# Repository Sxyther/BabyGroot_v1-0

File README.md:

# BabyGroot_v1-0
Babygroot project. Arduino based watering system for indoor plants

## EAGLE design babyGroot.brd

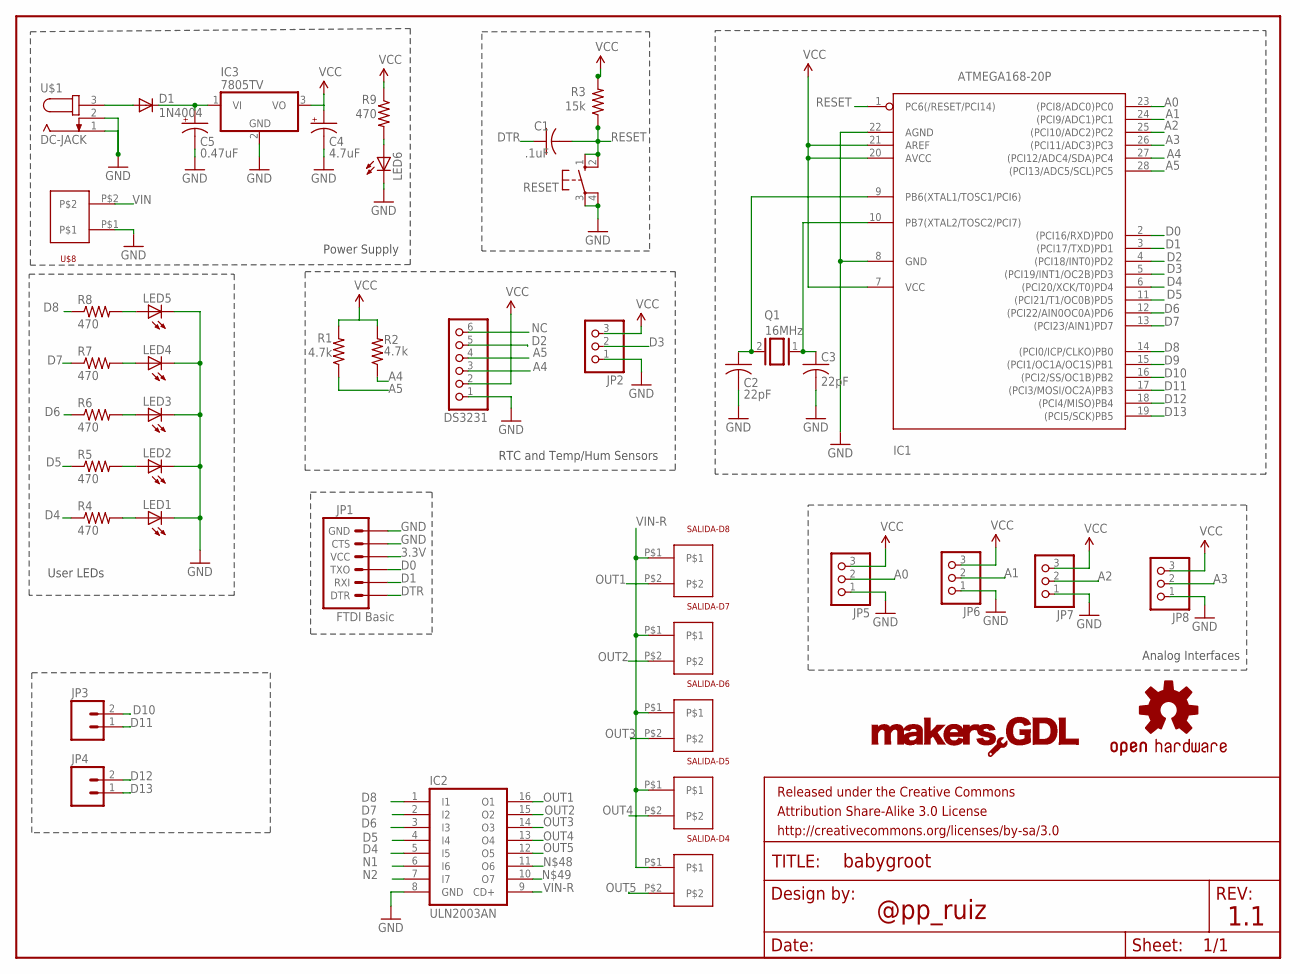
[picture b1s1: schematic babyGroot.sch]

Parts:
C1: .1uF; C025-024X044
C2, C3: 22pF; C025-024X044
C4: 4.7uF; E2,5-6E
C5: 0.47uF; E2,5-6E
D1: 1N4004; DO41-10
DS3231: PINHD-1X6; 1X06
FRAME1: FRAME-LETTER; CREATIVE_COMMONS
IC1: ATMEGA168-20P; DIL28-3
IC2: ULN2003AN; DIL16
IC3: 7805TV; TO220V
JP1: FTDI Basic; 1X06
JP2, JP5, JP6, JP7, JP8: PINHD-1X3; 1X03
JP3, JP4: M02PTH; 1X02
LED1, LED2, LED3, LED4, LED5, LED6: LED3MM
Q1: 16MHz; QS
R1, R2: 4.7k; 0204V
R3: 15k; 0204V
R4, R5, R6, R7, R8, R9: 470; 0204V
RESET: 10-XX; B3F-10XX
SALIDA-D4, SALIDA-D5, SALIDA-D6, SALIDA-D7, SALIDA-D8: 2POSHEADER-0.5MM; 2PIN-0.5MM
U$1: DC-JACK; SPC4078
U$3: OSHW-LOGOS; OSHW-LOGO-S
U$4: MAKERSGDLLOGO-SMALL; MAKERSGGL-SMALL
U$8: 2POSHEADER-0.5MM; 2PIN-0.5MM

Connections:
3.3V: C4.+, DS3231.2, IC1.7 (VCC), IC1.20 (AVCC), IC1.21 (AREF), IC3.3 (VO), JP1.4 (VCC), JP2.3, JP5.3, JP6.3, JP7.3, JP8.3, R1.2, R2.2, R3.2, R9.1
A0: IC1.23 ((PCI8/ADC0)PC0), JP5.2
A1: IC1.24 ((PCI9/ADC1)PC1), JP6.2
A2: IC1.25 ((PCI10/ADC2)PC2), JP7.2
A3: IC1.26 ((PCI11/ADC3)PC3), JP8.2
A4: DS3231.3, IC1.27 ((PCI12/ADC4/SDA)PC4), R2.1
A5: DS3231.4, IC1.28 ((PCI13/ADC5/SCL)PC5), R1.1
D0: IC1.2 ((PCI16/RXD)PD0), JP1.3 (TXO)
D1: IC1.3 ((PCI17/TXD)PD1), JP1.2 (RXI)
D2: DS3231.5, IC1.4 ((PCI18/INT0)PD2)
D3: IC1.5 ((PCI19/INT1/OC2B)PD3), JP2.2
D4: IC1.6 ((PCI20/XCK/T0)PD4), IC2.5 (I5), R4.1
D5: IC1.11 ((PCI21/T1/OC0B)PD5), IC2.4 (I4), R5.1
D6: IC1.12 ((PCI22/AIN0OC0A)PD6), IC2.3 (I3), R6.1
D7: IC1.13 ((PCI23/AIN1)PD7), IC2.2 (I2), R7.1
D8: IC1.14 ((PCI0/ICP/CLKO)PB0), IC2.1 (I1), R8.1
D9: IC1.15 ((PCI1/OC1A/OC1S)PB1)
D10: IC1.16 ((PCI2/SS/OC1B)PB2), JP3.2
D11: IC1.17 ((PCI3/MOSI/OC2A)PB3), JP3.1
D12: IC1.18 ((PCI4/MISO)PB4), JP4.2
D13: IC1.19 ((PCI5/SCK)PB5), JP4.1
DTR: C1.1, JP1.1 (DTR)
GND: C2.2, C3.2, C4.-, C5.-, DS3231.1, IC1.8 (GND), IC1.22 (AGND), IC2.8 (GND), IC3.2 (GND), JP1.5 (CTS), JP1.6 (GND), JP2.1, JP5.1, JP6.1, JP7.1, JP8.1, LED1.K (C), LED2.K (C), LED3.K (C), LED4.K (C), LED5.K (C), LED6.K (C), RESET.3, RESET.4 (P1), U$1.1, U$1.2, U$8.P$1
N1: IC2.6 (I6)
N2: IC2.7 (I7)
unnamed: C2.1, IC1.9 (PB6(XTAL1/TOSC1/PCI6)), Q1.2
unnamed: C3.1, IC1.10 (PB7(XTAL2/TOSC2/PCI7)), Q1.1
unnamed: LED6.A, R9.2
unnamed: LED5.A, R8.2
unnamed: LED4.A, R7.2
unnamed: LED3.A, R6.2
unnamed: LED2.A, R5.2
unnamed: LED1.A, R4.2
NC: DS3231.6
OUT1: IC2.16 (O1), SALIDA-D8.P$2
OUT2: IC2.15 (O2), SALIDA-D7.P$2
OUT3: IC2.14 (O3), SALIDA-D6.P$2
OUT4: IC2.13 (O4), SALIDA-D5.P$2
OUT5: IC2.12 (O5), SALIDA-D4.P$2
RESET: C1.2, IC1.1 (PC6(/RESET/PCI14)), R3.1, RESET.1 (S), RESET.2 (S1)
VIN: D1.A, U$1.3, U$8.P$2
VIN-R: C5.+, D1.C, IC2.9 (CD+), IC3.1 (VI), SALIDA-D4.P$1, SALIDA-D5.P$1, SALIDA-D6.P$1, SALIDA-D7.P$1, SALIDA-D8.P$1

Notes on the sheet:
User LEDs
@pp_ruiz
1.1
Power Supply
RTC and Temp/Hum Sensors
Analog Interfaces

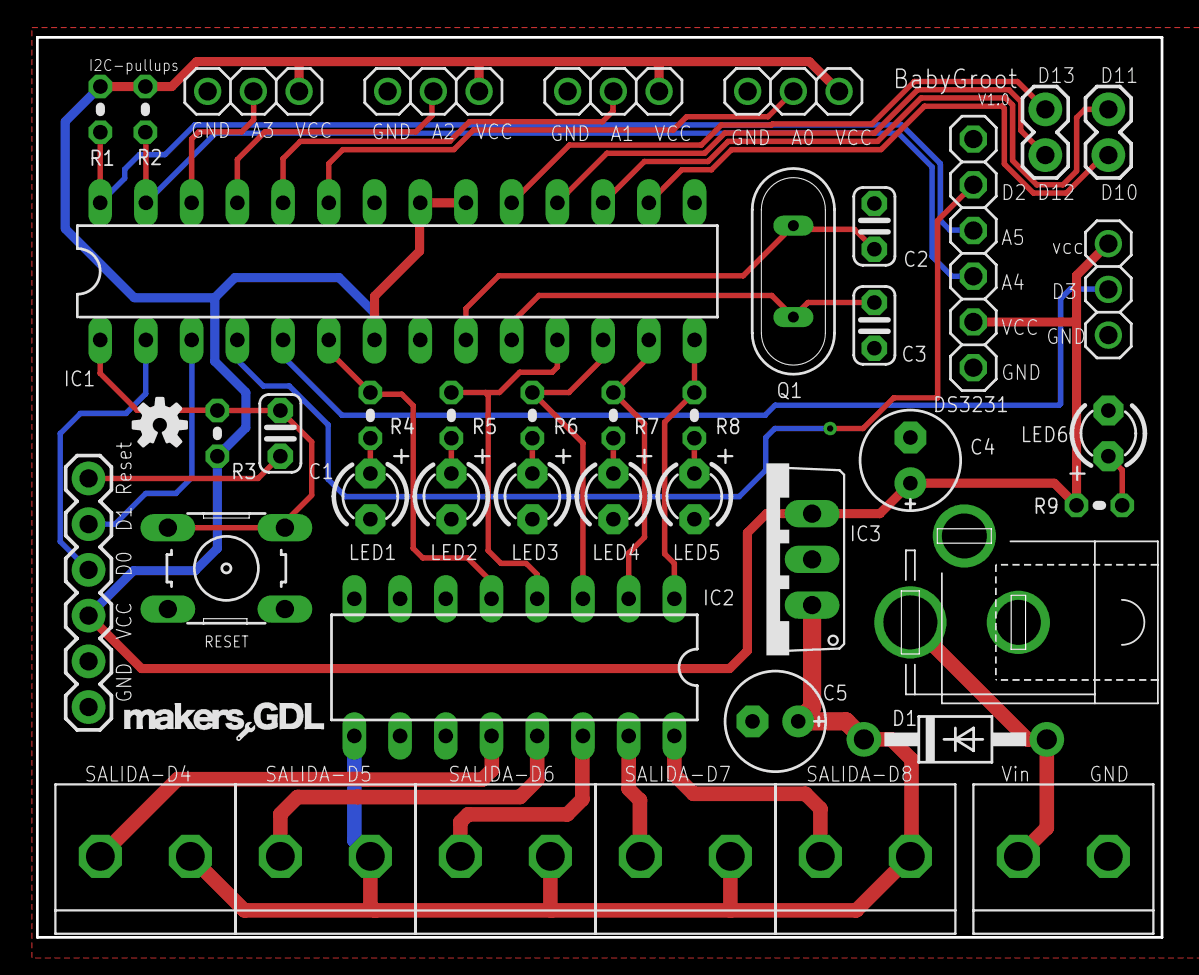
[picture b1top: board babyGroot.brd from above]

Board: 2 copper layers, 62.5 x 50.0 mm, 45 parts (0 on the bottom side), 38 nets.

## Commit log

2018-12-04 Add files via upload
    supports more than 8 alarms

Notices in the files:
parts and their libraries:
SparkFun-Aesthetics: Licensing: CC v3.0 Share-Alike You are welcome to use this library for commercial purposes.
SparkFun-Aesthetics: Released under the Creative Commons Attribution Share-Alike 3.0 License
SparkFun-Aesthetics: http://creativecommons.org/licenses/by-sa/3.0
